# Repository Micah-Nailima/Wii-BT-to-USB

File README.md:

# Wii BT to USB
 A conversion for Wii bluetooth adapters to be used via USB on PC's
 PCB's for both the WML-C43 and J27H002 bluetooth adapters found within the Nintendo Wii

WML-C43 is a Kicad Project
Wii Bluetooth Module is an Eagle project (i know, someone's gonna get mad cause I use both)

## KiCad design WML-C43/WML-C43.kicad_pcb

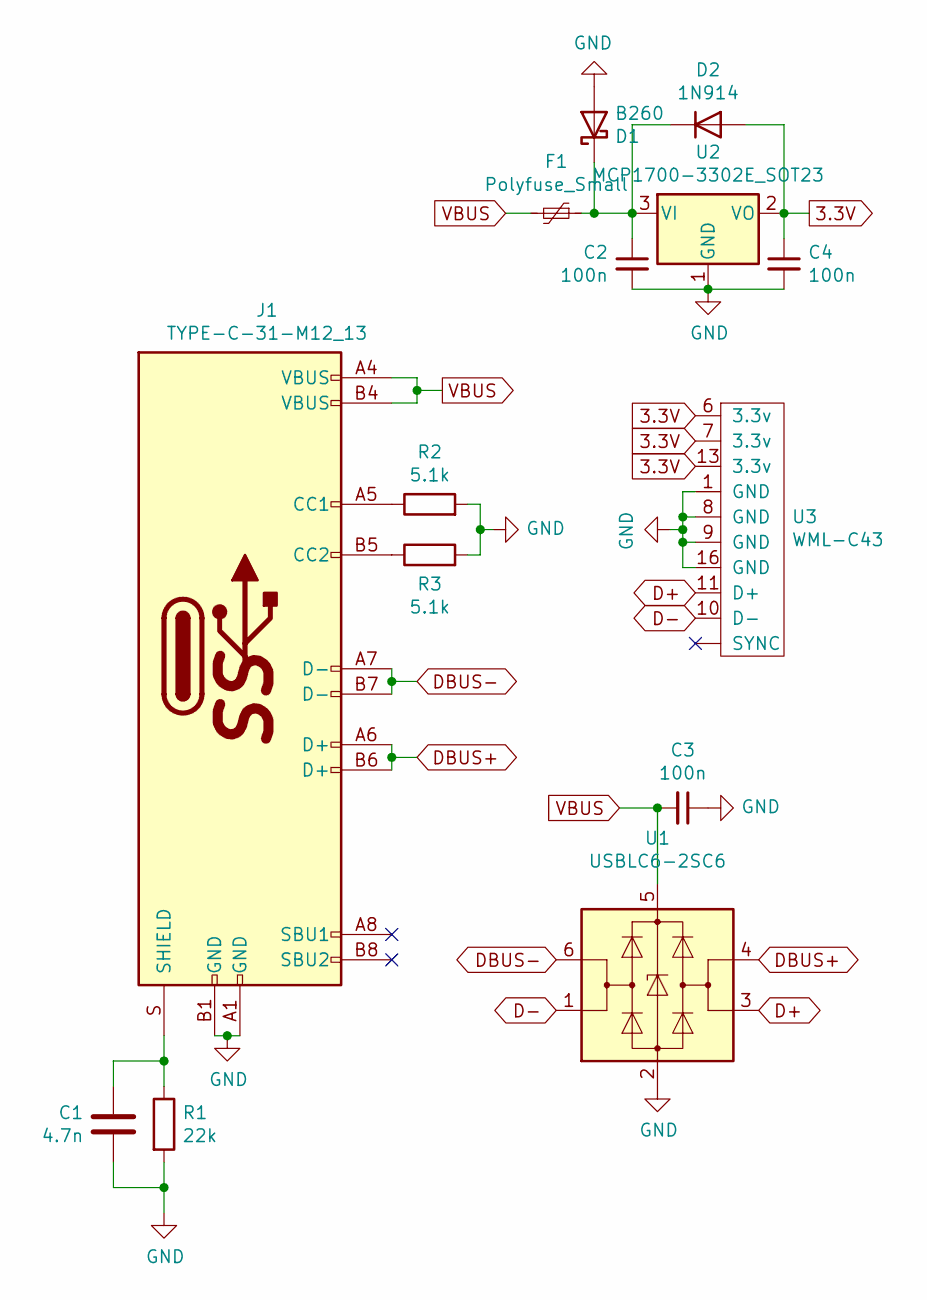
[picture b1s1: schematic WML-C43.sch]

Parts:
C1: 4.7n; C_0805_2012Metric_Pad1.15x1.40mm_HandSolder
C2, C3, C4: 100n; C_0805_2012Metric_Pad1.15x1.40mm_HandSolder
D1: B260; D_SMB
D2: 1N914; D_DO-35_SOD27_P7.62mm_Horizontal
F1: Polyfuse_Small; Fuse_1206_3216Metric_Pad1.42x1.75mm_HandSolder
J1: TYPE-C-31-M12_13; TYPE-C-31-M-12
R1: 22k; R_0805_2012Metric_Pad1.15x1.40mm_HandSolder
R2, R3: 5.1k; R_0805_2012Metric_Pad1.15x1.40mm_HandSolder
U1: USBLC6-2SC6; SOT-23-6
U2: MCP1700-3302E_SOT23; SOT-23
U3: WML-C43

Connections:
3.3V: C4.1, D2.2 (A), U2.2 (VO), U3.6 (3.3v), U3.7 (3.3v), U3.13 (3.3v)
D+: U1.3 (I/O2), U3.11 (D+)
D-: U1.1 (I/O1), U3.10 (D-)
DBUS+: J1.A6 (D+), J1.B6 (D+), U1.4 (I/O2)
DBUS-: J1.A7 (D-), J1.B7 (D-), U1.6 (I/O1)
GND: C1.2, C2.2, C3.1, C4.2, D1.2 (A), J1.A1 (GND), J1.B1 (GND), R1.2, R2.2, R3.2, U1.2 (GND), U2.1 (GND), U3.1 (GND), U3.8 (GND), U3.9 (GND), U3.16 (GND)
unnamed: C1.1, J1.S (SHIELD), R1.1
unnamed: C2.1, D1.1 (K), D2.1 (K), F1.1, U2.3 (VI)
unnamed: J1.A5 (CC1), R2.1
unnamed: J1.B5 (CC2), R3.1
VBUS: C3.2, F1.2, J1.A4 (VBUS), J1.B4 (VBUS), U1.5 (VBUS)

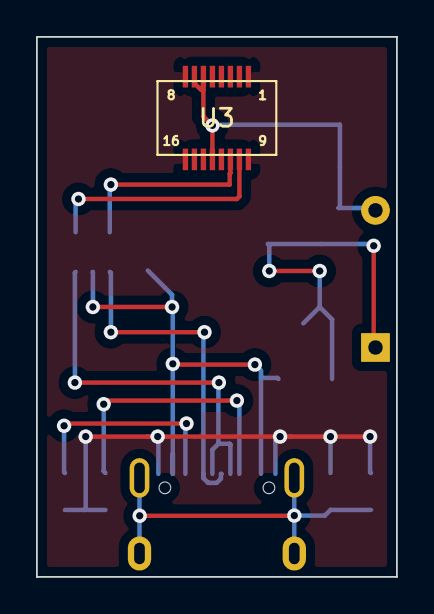
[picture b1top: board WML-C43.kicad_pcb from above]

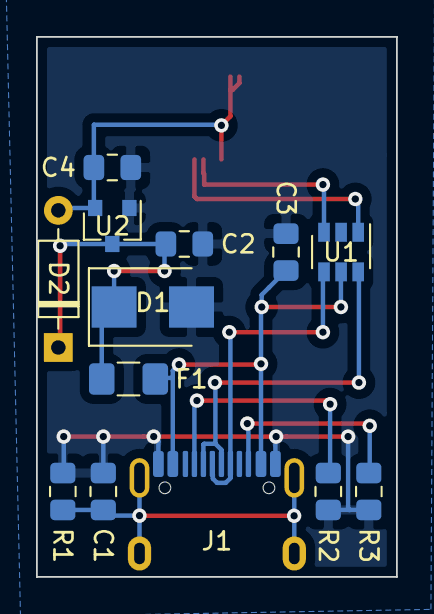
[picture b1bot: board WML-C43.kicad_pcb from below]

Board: 2 copper layers, 20.0 x 30.0 mm, 14 parts (13 on the bottom side), 11 nets.

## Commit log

2020-08-06 Added AcheronLibrary
2020-08-06 WML-C43
    added libraries
    added project files
2020-08-07 power supply and esd protection
2020-09-03 50% done
    +footprint and symbol for WML-C43 Molex Connector
    +pcb
    +schematic finished
2020-09-27 uploaded original eagle project
2020-10-07 eagle project updated
2020-11-12 pcb finish i think
2021-03-12 v0.4
    -added USB data pin ESD protection
    -added low pass filter to deal with noise on VCC/+5v
    -fixed the slim stack connector pinout cause the 1-8 row was flipped because my brain is pepega
2021-03-12 removed gerbers
2021-03-12 Update fp-info-cache
